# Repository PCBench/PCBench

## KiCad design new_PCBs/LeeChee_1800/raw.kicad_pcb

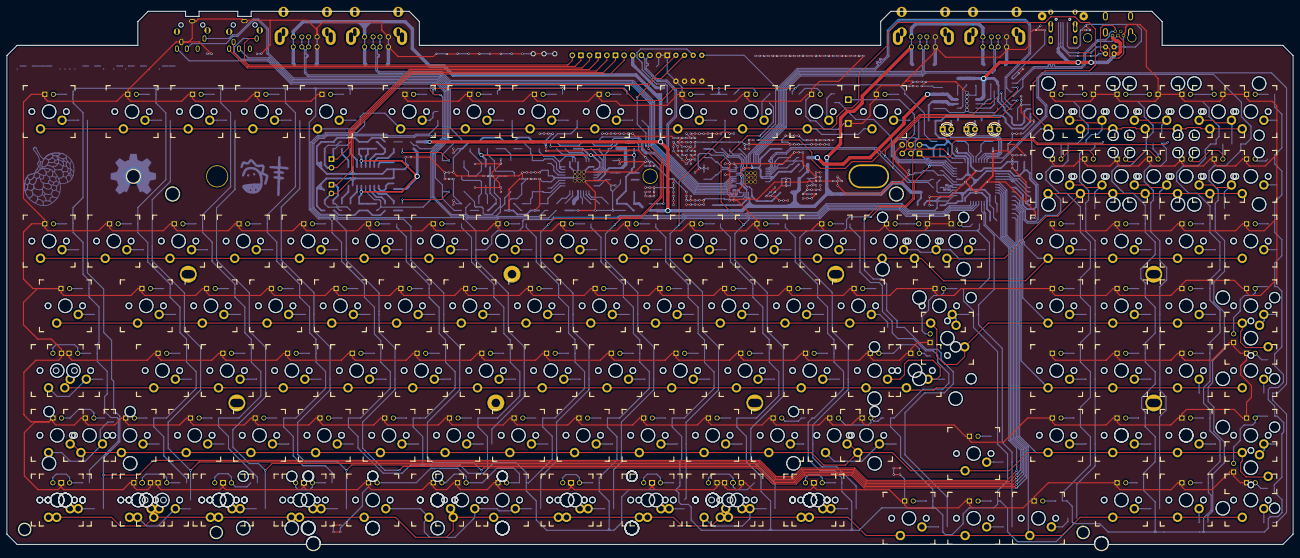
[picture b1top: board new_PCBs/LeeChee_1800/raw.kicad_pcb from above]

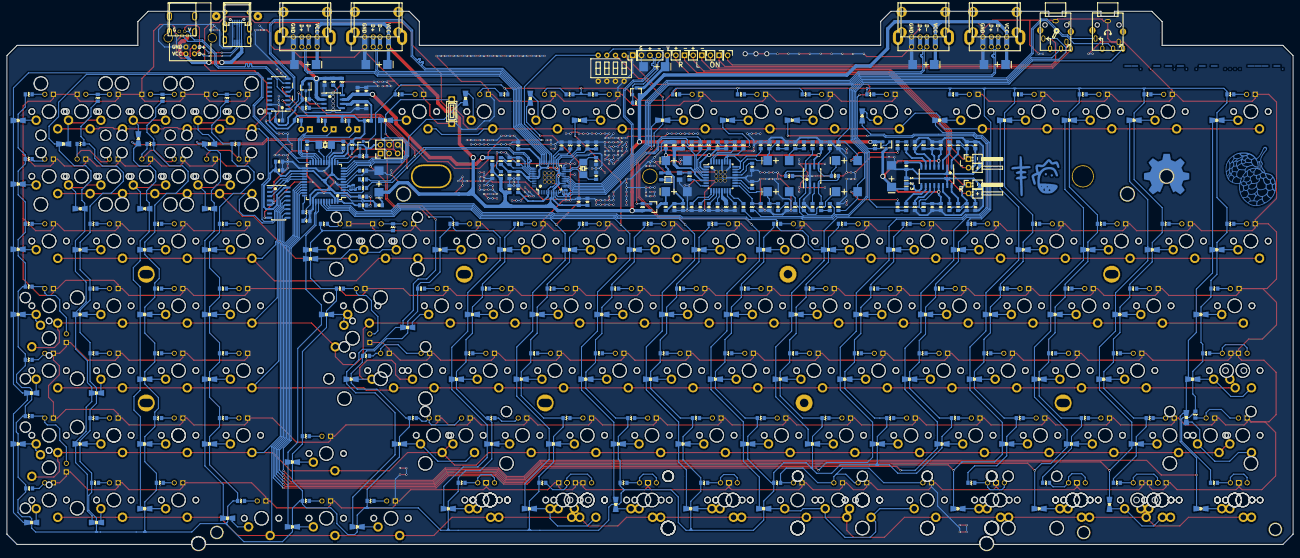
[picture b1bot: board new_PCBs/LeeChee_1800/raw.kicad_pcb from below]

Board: 2 copper layers, 378.4 x 158.6 mm, 557 parts (389 on the bottom side), 358 nets.

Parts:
C1, C2, C73, C74: 22pF; C_0805
C3, C8, C19, C20, C21, C29, C36, C38, C39, C40, C43, C44, C50, C52, C54, C55, C56, C57, C62, C63, C64, C65: 1uF; C_0805
C4, C5, C6, C7, C12, C13, C14, C15, C16, C17, C18, C35, C59, C68, C69, C70, C76: 0.1uF; C_0805
C9, C11, C45, C51, C53: 10uF; C_0805
C10: 4.7uF; C_0805
C22, C23, C24, C25, C26, C27, C28, C41, C42, C58, C75: 100uF; Tantalum_D_7343
C32, C33: 100pF; C_0805
C34, C37: 3.3uF; C_0805
C46, C47, C48, C49: 220pF; C_0805
C60, C61: 22nF; C_0805
C66, C67: 330uF; Tantalum_D_7343
C71, C72: 22uF; C_0805
D1, D2: 1N5817; D_0805
DOWN1: CONN_01X04; Pin_Header_Straight_1x04_Pitch2.54mm
DOWN2, DOWN3, DOWN5, DOWN6: USB_A
DOWN2_2, DOWN3_2, DOWN5_2, DOWN6_2: USB_A; USB_A_10mm
FB1, FB2, FB3, FB4: 2A/120; L_0805
HEADPHONE1: PJ-343
HOLE1: HOLE; OSHW-Symbol_13.4x12mm_Copper
HOLE1_2, HOLE2, HOLE4, HOLE6, HOLE10, HOLE11: HOLE; HOLE_4mm
HOLE3: HOLE; HOLE_6mm
HOLE5: HOLE; HOLE_6X11MM
HOLE7, HOLE8, HOLE9: HOLE; HOLE_3.5mm
J1: JUMP3; JUMP3_0805_Hand
J2: CONN_01X02; Pin_Header_Straight_1x02_Pitch2.54mm
J3: CONN_01X01; Pin_Header_Straight_1x01_Pitch2.54mm
KBD1, KBD2, KBD3, KBD4, KBD5, KBD6, KBD7, KBD8, KBD9, KBD10, KBD11, KBD12, KBD13, KBD14, KBD15, KBD16, KBD17, KBD18, KBD19, KBD20, KBD21, KBD22, KBD23, KBD24, KBD25, KBD26, KBD27, KBD28, KBD29, KBD30, KBD31, KBD32, KBD33, KBD34, KBD35, KBD36, KBD37, KBD38, KBD39, KBD40, KBD41, KBD42, KBD43, KBD44, KBD45, KBD46, KBD47, KBD48, KBD49, KBD50, KBD51, KBD52, KBD53, KBD54, KBD55, KBD56, KBD57, KBD58, KBD59, KBD60, KBD61, KBD62, KBD63, KBD64, KBD65, KBD66, KBD67, KBD68, KBD69, KBD70, KBD71, KBD72, KBD73, KBD74, KBD75, KBD76, KBD77, KBD78, KBD79, KBD80, KBD81, KBD82, KBD83, KBD84, KBD85, KBD86, KBD87, KBD88, KBD89, KBD90, KBD91, KBD92, KBD93, KBD94, KBD95, KBD96, KBD97, KBD98, KBD99, KBD100, KBD101, KBD102, KBD103, KBD104, KBD105, KBD106, KBD107, KBD108: 4148; D_0805&LL4148
KBR1, KBR2, KBR3, KBR4, KBR5, KBR6, KBR7, KBR8, KBR9, KBR10, KBR11, KBR12, KBR13, KBR14, KBR15, KBR16, KBR17, KBR18, KBR19, KBR20, KBR21, KBR22, KBR23, KBR24, KBR25, KBR26, KBR27, KBR28, KBR29, KBR30, KBR31, KBR32, KBR33, KBR34, KBR35, KBR36, KBR37, KBR38, KBR39, KBR40, KBR41, KBR42, KBR43, KBR44, KBR45, KBR46, KBR47, KBR48, KBR49, KBR50, KBR51, KBR52, KBR53, KBR54, KBR55, KBR56, KBR57, KBR58, KBR59, KBR60, KBR61, KBR62, KBR63, KBR64, KBR65, KBR66, KBR67, KBR68, KBR69, KBR70, KBR71, KBR72, KBR73, KBR74, KBR75, KBR76, KBR77, KBR78, KBR79, KBR80, KBR81, KBR82, KBR83, KBR84, KBR85, KBR86, KBR87, KBR88, KBR89, KBR90, KBR91, KBR92, KBR93, KBR94, KBR95, KBR96, KBR97, KBR98, KBR99, KBR100, KBR101, KBR102, KBR103, KBR104, KBR105, KBR106, KBR107, KBR108: 330R; R_0805
KB_ICSP1: AVR-ISP-6; Pin_Header_Straight_2x03_Pitch2.54mm
L1, L2: 1uH; L_0805
LED1, LED2, LED3: LED; LED_D3.0mm
LED5, LED6: LED; LED_0805
MICROPHONE1: PJ-343
MX_0_1, MX_1_1, MX_2_1, MX_3_1, MX_4_1, MX_5_1, MX_6_1, MX_7_1, MX_8_1, MX_9_1, MX_._1: CherryMX; MX1-X-led
MX_'_1: CherryMX; MX1-X-led
MX_,_1: CherryMX; MX1-X-led
MX_-_1: CherryMX; MX1-X-led
MX_/_1: CherryMX; MX1-X-led
MX_;_1: CherryMX; MX1-X-led
MX_=_1: CherryMX; MX1-X-led
MX_ADD_1: CherryMX; MX1-B-led
MX_ADD_2: CherryMX; MX1-X-led
MX_APP_1: CherryMX; MX1-C-led
MX_APP_2: CherryMX; MX1-X-led
MX_APP_3: CherryMX; MX1-B-led
MX_A_1: CherryMX; MX1-X-led
MX_BSPC2: CherryMX; MX1-X-led
MX_BSPC_1: CherryMX; MX1-X-led
MX_BSPC_2: CherryMX; MX1-B-led
MX_B_1: CherryMX; MX1-X-led
MX_CAPS_1: CherryMX; MX1-C-led
MX_CAPS_2: CherryMX; MX1-X-led
MX_C_1: CherryMX; MX1-X-led
MX_DEL_1, MX_DEL_2: CherryMX; MX1-X-led
MX_DOWN_1: CherryMX; MX1-X-led
MX_D_1: CherryMX; MX1-X-led
MX_END_1, MX_END_2: CherryMX; MX1-X-led
MX_ENT_1, MX_ENT_2: CherryMX; MX1-X-led
MX_ESC_1: CherryMX; MX1-X-led
MX_E_1: CherryMX; MX1-X-led
MX_F1_1, MX_F2_1, MX_F3_1, MX_F4_1, MX_F5_1, MX_F6_1, MX_F7_1, MX_F8_1, MX_F9_1, MX_F10_1, MX_F11_1, MX_F12_1: CherryMX; MX1-X-led
MX_FRAME_BSPC_1: MX_FRAME_HOLE; MX_FRAME_2X
MX_FRAME_DEL_1: MX_FRAME_HOLE; MX_FRAME_2X
MX_FRAME_END_1: MX_FRAME_HOLE; MX_FRAME_2X
MX_FRAME_ENT_1: MX_FRAME_HOLE; MX_FRAME_2X
MX_FRAME_HOME_1: MX_FRAME_HOLE; MX_FRAME_2X
MX_FRAME_INS_1: MX_FRAME_HOLE; MX_FRAME_2X
MX_FRAME_LSFT_1: MX_FRAME_HOLE; MX_FRAME_2X
MX_FRAME_P-_1: MX_FRAME_HOLE; MX_FRAME_2X
MX_FRAME_PENT_1: MX_FRAME_HOLE; MX_FRAME_2X
MX_FRAME_PGDN_1: MX_FRAME_HOLE; MX_FRAME_2X
MX_FRAME_PGUP_1: MX_FRAME_HOLE; MX_FRAME_2X
MX_FRAME_RSFT_1: MX_FRAME_HOLE; MX_FRAME_2X
MX_FRAME_SPC_1, MX_FRAME_SPC_2, MX_FRAME_SPC_3: MX_FRAME_HOLE; MX_FRAME_3X
MX_FRAME_SPC_4: MX_FRAME_HOLE; MX_FRAME_6X
MX_FRAME_SPC_5: MX_FRAME_HOLE; MX_FRAME_6.25X
MX_FRAME_SPC_6: MX_FRAME_HOLE; MX_FRAME_7X
MX_FRAME_\_1: MX_FRAME_HOLE; MX_FRAME_2X
MX_F_1: CherryMX; MX1-X-led
MX_GRV_1: CherryMX; MX1-X-led
MX_G_1: CherryMX; MX1-X-led
MX_HOME_1: CherryMX; MX1-X-led
MX_HOME_2: CherryMX; MX1-B-led
MX_H_1: CherryMX; MX1-X-led
MX_INS_1: CherryMX; MX1-X-led
MX_INS_2: CherryMX; MX1-B-led
MX_I_1: CherryMX; MX1-X-led
MX_J_1: CherryMX; MX1-X-led
MX_K_1: CherryMX; MX1-X-led
MX_LALT_1: CherryMX; MX1-B-led
MX_LALT_2: CherryMX; MX1-X-led
MX_LCTL_1: CherryMX; MX1-B-led
MX_LCTL_2: CherryMX; MX1-X-led
MX_LEFT_1: CherryMX; MX1-X-led
MX_LGUI_1: CherryMX; MX1-A-led
MX_LGUI_2: CherryMX; MX1-C-led
MX_LGUI_3: CherryMX; MX1-X-led
MX_LSFT2: CherryMX; MX1-X-led
MX_LSFT_1: CherryMX; MX1-A-led
MX_LSFT_2: CherryMX; MX1-X-led
MX_L_1: CherryMX; MX1-X-led
MX_M_1: CherryMX; MX1-X-led
MX_NLCK_1: CherryMX; MX1-X-led
MX_N_1: CherryMX; MX1-X-led
MX_O_1: CherryMX; MX1-X-led
MX_P0_1, MX_P1_1, MX_P2_1, MX_P3_1, MX_P4_1, MX_P5_1, MX_P6_1, MX_P7_1, MX_P8_1, MX_P9_1, MX_P._1: CherryMX; MX1-X-led
MX_P*_1: CherryMX; MX1-X-led
MX_P+_1: CherryMX; MX1-X-led
MX_P-_1, MX_P-_2: CherryMX; MX1-X-led
MX_P/_1: CherryMX; MX1-X-led
MX_PAUS_1: CherryMX; MX1-X-led
MX_PENT2: CherryMX; MX1-X-led
MX_PENT_1, MX_PENT_2: CherryMX; MX1-X-led
MX_PGDN_1, MX_PGDN_2: CherryMX; MX1-X-led
MX_PGUP_1: CherryMX; MX1-X-led
MX_PGUP_2: CherryMX; MX1-B-led
MX_PRSC_1: CherryMX; MX1-X-led
MX_P_1: CherryMX; MX1-X-led
MX_Q_1: CherryMX; MX1-X-led
MX_RALT_1: CherryMX; MX1-B-led
MX_RALT_2: CherryMX; MX1-X-led
MX_RCTL_1: CherryMX; MX1-B-led
MX_RCTL_2: CherryMX; MX1-X-led
MX_RGHT_1: CherryMX; MX1-X-led
MX_RGUI_1: CherryMX; MX1-B-led
MX_RGUI_2: CherryMX; MX1-X-led
MX_RSFT_1: CherryMX; MX1-A-led
MX_RSFT_2: CherryMX; MX1-X-led
MX_R_1: CherryMX; MX1-X-led
MX_SLCK_1: CherryMX; MX1-X-led
MX_SPC_1, MX_SPC_3, MX_SPC_4: CherryMX; MX1-X-led
MX_SPC_2: CherryMX; MX1-A-led
MX_S_1: CherryMX; MX1-X-led
MX_TAB_1: CherryMX; MX1-X-led
MX_T_1: CherryMX; MX1-X-led
MX_UP_1: CherryMX; MX1-X-led
MX_U_1: CherryMX; MX1-X-led
MX_V_1: CherryMX; MX1-X-led
MX_W_1: CherryMX; MX1-X-led
MX_X_1: CherryMX; MX1-X-led
MX_Y_1: CherryMX; MX1-X-led
MX_Z_1: CherryMX; MX1-X-led
MX_[_1: CherryMX; MX1-X-led
MX_\_1, MX_\_2: CherryMX; MX1-X-led
MX_]_1: CherryMX; MX1-X-led
Q1, Q2, Q3, Q4, Q5: SI2305; SOT-23
R1, R2: 22R; R_0805
R3, R4, R5, R26, R27, R28, R42, R43, R44, R45, R46, R47: 10kR; R_0805
R6, R7, R8: 330R; R_0805
R9, R12: 100kR; R_0805
R10: 2.7kR; R_0805
R11: 47kR; R_0805
R13, R14: 33R; R_0805
R15: 1.5kR; R_0805
R17: 1kR; R_0805
R18, R19, R20, R21: 3.3kR; R_0805
R22, R23: 820R; R_0805
R24, R39, R40: 0R; R_0805
R25, R48: 10R; R_0805
R29, R30: 16R; R_0805
R31, R32, R33, R34, R35, R36: 20kR; R_0805
R37, R38: 100R; R_0805
R41: 10KR; R_0805
SP1, SP2: Speaker; Pin_Header_Angled_1x02_Pitch2.54mm
SP1_2, SP2_2: CONN_01X02; Pin_Header_Straight_1x02_Pitch2.54mm
SW2: SWITCH; SWITCH-3X6X2.5_SMD+
SW_ALLIN1: DIP4WAY; SW_DIP_x4_W7.62mm_Slide_LowProfile
U1: CH440G; SOIC-16_3.9x9.9mm_Pitch1.27mm
U2: ATMEGA32U4; TQFP-44_10x10mm_Pitch0.8mm
U3: 74HC138; SOIC-16_3.9x9.9mm_Pitch1.27mm
U4: FE2.1; LQFP-48_7x7mm_Pitch0.5mm
U5: PCM2912A; TQFP-32_7x7mm_Pitch0.8mm
U6: PAM8406; SOIC-16_3.9x9.9mm_Pitch1.27mm
U7: TPA152; SOIC-8_3.9x4.9mm_Pitch1.27mm
U8: TPS2062; SOIC-8_3.9x4.9mm_Pitch1.27mm
USB1: MINI_USB; USB_MINI_4FOOT
USB2: USB_B
USB3: USB_OTG; USB_MICRO_4FOOT_LONG
USB4: USB_OTG; USB_MICRO_4FOOT
Y1: 16MHz; X_SMD_5032-2pin_5.0x3.2mm
Y2: 12MHz; X_SMD_5032-2pin_5.0x3.2mm
Y4: 6MHz; X_SMD_5032-4pin_5.0x3.2mm

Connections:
/3TO8IO1: U2.25, U3.1
/3TO8IO2: U2.26, U3.2
/3TO8IO3: U2.27, U3.3
/COL1: KBD1.2, KBD23.2, KBD41.2, KBD60.2, KBD77.2, KBD95.2, U2.36
/COL2: KBD2.2, KBD24.2, KBD42.2, KBD61.2, KBD78.2, KBD96.2, U2.32
/COL3: KBD3.2, KBD25.2, KBD43.2, KBD62.2, KBD79.2, KBD97.2, U2.31
/COL4: KBD4.2, KBD26.2, KBD45.2, KBD63.2, KBD80.2, KBD98.2, U2.30
/COL5: KBD5.2, KBD27.2, KBD46.2, KBD64.2, KBD81.2, U2.29
/COL6: KBD6.2, KBD28.2, KBD47.2, KBD65.2, KBD82.2, U2.28
/COL7: KBD7.2, KBD29.2, KBD48.2, KBD66.2, KBD83.2, U2.1
/COL8: KBD8.2, KBD30.2, KBD49.2, KBD67.2, KBD84.2, KBD99.2, U2.41
/COL9: KBD9.2, KBD31.2, KBD50.2, KBD68.2, KBD85.2, KBD100.2, U2.40
/COL10: KBD10.2, KBD32.2, KBD51.2, KBD69.2, KBD86.2, KBD101.2, U2.39
/COL11: KBD11.2, KBD33.2, KBD52.2, KBD70.2, KBD87.2, KBD102.2, U2.38
/COL12: KBD12.2, KBD34.2, KBD53.2, KBD71.2, KBD88.2, KBD103.2, U2.8
/COL13: KBD13.2, KBD35.2, KBD54.2, KBD72.2, KBD89.2, KBD104.2, KB_ICSP1.3, U2.9
/COL14: KBD18.2, KBD36.2, KBD55.2, KBD90.2, KBD105.2, U2.37
/COL15: KBD14.2, KBD19.2, KBD37.2, KBD56.2, KBD73.2, KBD91.2, KBD106.2, KB_ICSP1.4, U2.10
/COL16: KBD15.2, KBD20.2, KBD38.2, KBD57.2, KBD74.2, KBD92.2, KBD107.2, KB_ICSP1.1, U2.11
/COL17: KBD16.2, KBD21.2, KBD39.2, KBD58.2, KBD75.2, KBD93.2, KBD108.2, U2.22
/COL18: KBD17.2, KBD22.2, KBD40.2, KBD44.2, KBD59.2, KBD76.2, KBD94.2, U2.21
/DC5V: C10.1, C13.1, C23.1, C24.1, C26.1, C27.1, C28.1, D2.2, DOWN2.1, DOWN2_2.1, DOWN3.1, DOWN3_2.1, DOWN5.1, DOWN5_2.1, DOWN6.1, DOWN6_2.1, L1.1, Q2.2, Q4.2, Q5.2, R11.2, R41.1, R42.2, R47.2, U4.8
/DOWN1+: DOWN1.3, U4.19
/DOWN1-: DOWN1.2, U4.18
/DOWN1_DC5V: C22.1, DOWN1.1, Q2.3
/DOWN2+: DOWN2.3, DOWN2_2.3, U4.17
/DOWN2-: DOWN2.2, DOWN2_2.2, U4.16
/DOWN3+: DOWN3.3, DOWN3_2.3, U4.14
/DOWN3-: DOWN3.2, DOWN3_2.2, U4.13
/DOWN4+: R14.1, R15.1, U4.12
/DOWN4-: R13.1, U4.11
/DOWN5+: DOWN5.3, DOWN5_2.3, U4.33
/DOWN5-: DOWN5.2, DOWN5_2.2, U4.32
/DOWN6+: DOWN6.3, DOWN6_2.3, U4.35
/DOWN6-: DOWN6.2, DOWN6_2.2, U4.34
/DOWN7+: R1.2, U1.3, U4.38
/DOWN7-: R2.2, U1.6, U4.37
/DOWN_1_ON: Q2.1, R42.1, SW_ALLIN1.3
/EN1: Q1.1, R43.2, SW_ALLIN1.4, U1.1, U8.3
/EN2: Q1.3, R44.2, U8.4
/HUBUSBD+: U1.2, U4.30
/HUBUSBD-: U1.5, U4.29
/HUBVCC: C69.2, C71.2, L1.2, U8.7
/HUBX+: C73.1, U4.22, Y2.1
/HUBX-: C74.1, U4.23, Y2.2
/KBBL: Q3.1, R5.2, U2.12
/KBRST: KB_ICSP1.5, R4.2, SW2.1, U2.13
/KBVCC: C4.1, C5.1, C6.1, C7.1, C8.1, D1.1, D2.1, KB_ICSP1.2, Q3.2, R4.1, R5.1, R6.2, R7.2, R8.2, U2.2, U2.7, U2.14, U2.24, U2.34, U2.44, U3.6, U3.16
/KBX+: C1.1, U2.16, Y1.1
/KBX-: C2.1, U2.17, Y1.2
/KD+: R1.1, U2.4
/KD-: R2.1, U2.3
/LED+: KBR1.2, KBR2.2, KBR3.2, KBR4.2, KBR5.2, KBR6.2, KBR7.2, KBR8.2, KBR9.2, KBR10.2, KBR11.2, KBR12.2, KBR13.2, KBR14.2, KBR15.2, KBR16.2, KBR17.2, KBR18.2, KBR19.2, KBR20.2, KBR21.2, KBR22.2, KBR23.2, KBR24.2, KBR25.2, KBR26.2, KBR27.2, KBR28.2, KBR29.2, KBR30.2, KBR31.2, KBR32.2, KBR33.2, KBR34.2, KBR35.2, KBR36.2, KBR37.2, KBR38.2, KBR39.2, KBR40.2, KBR41.2, KBR42.2, KBR43.2, KBR44.2, KBR45.2, KBR46.2, KBR47.2, KBR48.2, KBR49.2, KBR50.2, KBR51.2, KBR52.2, KBR53.2, KBR54.2, KBR55.2, KBR56.2, KBR57.2, KBR58.2, KBR59.2, KBR60.2, KBR61.2, KBR62.2, KBR63.2, KBR64.2, KBR65.2, KBR66.2, KBR67.2, KBR68.2, KBR69.2, KBR70.2, KBR71.2, KBR72.2, KBR73.2, KBR74.2, KBR75.2, KBR76.2, KBR77.2, KBR78.2, KBR79.2, KBR80.2, KBR81.2, KBR82.2, KBR83.2, KBR84.2, KBR85.2, KBR86.2, KBR87.2, KBR88.2, KBR89.2, KBR90.2, KBR91.2, KBR92.2, KBR93.2, KBR94.2, KBR95.2, KBR96.2, KBR97.2, KBR98.2, KBR99.2, KBR100.2, KBR101.2, KBR102.2, KBR103.2, KBR104.2, KBR105.2, KBR106.2, KBR107.2, KBR108.2, Q3.3
/LEDC: LED2.1, U2.19
/LEDN: LED1.1, U2.18
/LEDS: LED3.1, U2.20
/MICMBIAS: MICROPHONE1.R, R17.2
/MICVIN: C37.2, J3.1, MICROPHONE1.L
/PAINL: C55.2, C67.2, HEADPHONE1.L, R38.1
/PAINR: C56.2, C66.2, HEADPHONE1.R, R37.1
/PAMODE: J1.2, U6.9
/PAMUTE: C50.2, C51.2, C52.2, C53.2, C58.1, J1.3, Q4.3, R25.1, R28.1, U6.4, U6.5, U6.13
/PASHDN: HEADPHONE1.ON, R28.2, U6.12
/PA_ON: Q4.1, R47.1, SW_ALLIN1.1
/REXT: R10.1, U4.27
/ROW1: MX_ESC_1.2, MX_F1_1.2, MX_F2_1.2, MX_F3_1.2, MX_F4_1.2, MX_F5_1.2, MX_F6_1.2, MX_F7_1.2, MX_F8_1.2, MX_F9_1.2, MX_F10_1.2, MX_F11_1.2, MX_F12_1.2, MX_HOME_1.2, MX_HOME_2.2, MX_INS_1.2, MX_INS_2.2, MX_PGUP_1.2, MX_PGUP_2.2, MX_PRSC_1.2, U3.15
/ROW2: MX_BSPC2.2, MX_DEL_1.2, MX_DEL_2.2, MX_END_1.2, MX_END_2.2, MX_PGDN_1.2, MX_PGDN_2.2, MX_SLCK_1.2, U3.14
/ROW3: MX_0_1.2, MX_1_1.2, MX_2_1.2, MX_3_1.2, MX_4_1.2, MX_5_1.2, MX_6_1.2, MX_7_1.2, MX_8_1.2, MX_9_1.2, MX_-_1.2, MX_=_1.2, MX_BSPC_1.2, MX_BSPC_2.2, MX_GRV_1.2, MX_NLCK_1.2, MX_P*_1.2, MX_P/_1.2, MX_PAUS_1.2, U3.13
/ROW4: MX_E_1.2, MX_I_1.2, MX_O_1.2, MX_P7_1.2, MX_P8_1.2, MX_P9_1.2, MX_P-_1.2, MX_P-_2.2, MX_P_1.2, MX_Q_1.2, MX_R_1.2, MX_TAB_1.2, MX_T_1.2, MX_U_1.2, MX_W_1.2, MX_Y_1.2, MX_[_1.2, MX_\_1.2, MX_\_2.2, MX_]_1.2, U3.12
/ROW5: MX_'_1.2, MX_;_1.2, MX_A_1.2, MX_CAPS_1.2, MX_CAPS_2.2, MX_D_1.2, MX_ENT_1.2, MX_ENT_2.2, MX_F_1.2, MX_G_1.2, MX_H_1.2, MX_J_1.2, MX_K_1.2, MX_L_1.2, MX_P4_1.2, MX_P5_1.2, MX_P6_1.2, MX_P+_1.2, MX_S_1.2, U3.11
/ROW6: MX_,_1.2, MX_._1.2, MX_/_1.2, MX_B_1.2, MX_C_1.2, MX_LSFT2.2, MX_LSFT_1.2, MX_LSFT_2.2, MX_M_1.2, MX_N_1.2, MX_P1_1.2, MX_P2_1.2, MX_P3_1.2, MX_PENT_1.2, MX_PENT_2.2, MX_RSFT_1.2, MX_RSFT_2.2, MX_UP_1.2, MX_V_1.2, MX_X_1.2, MX_Z_1.2, U3.10
/ROW7: MX_ADD_1.2, MX_ADD_2.2, MX_APP_1.2, MX_APP_2.2, MX_APP_3.2, MX_DOWN_1.2, MX_LALT_1.2, MX_LALT_2.2, MX_LCTL_1.2, MX_LCTL_2.2, MX_LEFT_1.2, MX_LGUI_1.2, MX_LGUI_2.2, MX_LGUI_3.2, MX_P0_1.2, MX_P._1.2, MX_PENT2.2, MX_RALT_1.2, MX_RALT_2.2, MX_RCTL_1.2, MX_RCTL_2.2, MX_RGHT_1.2, MX_RGUI_1.2, MX_RGUI_2.2, MX_SPC_1.2, MX_SPC_2.2, MX_SPC_3.2, MX_SPC_4.2, U3.9
/SCD+: R14.2, U5.4
/SCD-: R13.2, U5.3
/SCDGND: C29.2, R24.1, U5.6
/SCOUTL: C41.2, C63.1, R20.1
/SCOUTR: C42.2, C62.1, R21.2
/SCPLAY: R23.2, U5.32
/SCREC: R22.2, U5.31
/SCVCC: C25.1, L2.2, Q5.3
/SCVCC2: C44.2, C45.1, C65.2, C75.1, C76.1, L2.1, LED5.2, LED6.2, U5.2, U7.6, Y4.4
/SCX+: R48.1, U5.8
/SC_ON: Q5.1, R41.2, SW_ALLIN1.2
/USBD+: U1.4, USB1.3, USB2.3, USB3.3, USB4.3
/USBD-: U1.7, USB1.2, USB2.2, USB3.2, USB4.2
/USBVCC: C59.1, C68.2, Q1.2, R43.1, R45.1, R46.2, U1.16, U8.2, USB1.1, USB2.1, USB3.1, USB4.1
/V18: C11.1, C19.1, C20.1, C21.1, U4.6, U4.21, U4.25, U4.28
/V33: C9.1, C14.1, C15.1, C16.1, C17.1, C18.1, R9.2, U4.9, U4.15, U4.20, U4.26, U4.31, U4.36, U4.42, U4.43, U4.45
/VBUSM: R11.1, R12.1, U4.41
/XRSTJ: C12.1, R9.1, U4.40
Earth: C1.2, C2.2, C3.2, C4.2, C5.2, C6.2, C7.2, C8.2, C9.2, C10.2, C11.2, C12.2, C13.2, C14.2, C15.2, C16.2, C17.2, C18.2, C19.2, C20.2, C21.2, C22.2, C23.2, C24.2, C25.2, C26.2, C27.2, C28.2, C32.2, C33.2, C34.2, C35.2, C36.2, C38.2, C39.1, C40.2, C43.2, C44.1, C45.2, C46.2, C47.1, C48.1, C49.2, C50.1, C51.1, C52.1, C53.1, C54.2, C57.2, C58.2, C59.2, C64.2, C65.1, C68.1, C69.1, C70.2, C71.1, C72.2, C73.2, C74.2, C75.2, C76.2, DOWN1.4, DOWN2.4, DOWN2_2.4, DOWN3.4, DOWN3_2.4, DOWN5.4, DOWN5_2.4, DOWN6.4, DOWN6_2.4, HEADPHONE1.G, HEADPHONE1.OS, J1.1, KB_ICSP1.6, MICROPHONE1.G, MX_0_1.4, MX_1_1.4, MX_2_1.4, MX_3_1.4, MX_4_1.4, MX_5_1.4, MX_6_1.4, MX_7_1.4, MX_8_1.4, MX_9_1.4, MX_'_1.4, MX_,_1.4, MX_-_1.4, MX_._1.4, MX_/_1.4, MX_;_1.4, MX_=_1.4, MX_ADD_1.4, MX_ADD_2.4, MX_APP_1.4, MX_APP_2.4, MX_APP_3.4, MX_A_1.4, MX_BSPC2.4, MX_BSPC_1.4, MX_BSPC_2.4, MX_B_1.4, MX_CAPS_1.4, MX_CAPS_2.4, MX_C_1.4, MX_DEL_1.4, MX_DEL_2.4, MX_DOWN_1.4, MX_D_1.4, MX_END_1.4, MX_END_2.4, MX_ENT_1.4, MX_ENT_2.4, MX_ESC_1.4, MX_E_1.4, MX_F1_1.4, MX_F2_1.4, MX_F3_1.4, MX_F4_1.4, MX_F5_1.4, MX_F6_1.4, MX_F7_1.4, MX_F8_1.4, MX_F9_1.4, MX_F10_1.4, MX_F11_1.4, MX_F12_1.4, MX_F_1.4, MX_GRV_1.4, MX_G_1.4, MX_HOME_1.4, MX_HOME_2.4, MX_H_1.4, MX_INS_1.4, MX_INS_2.4, MX_I_1.4, MX_J_1.4, MX_K_1.4, MX_LALT_1.4, MX_LALT_2.4, MX_LCTL_1.4, MX_LCTL_2.4, MX_LEFT_1.4, MX_LGUI_1.4, MX_LGUI_2.4, MX_LGUI_3.4, MX_LSFT2.4, MX_LSFT_1.4, MX_LSFT_2.4, MX_L_1.4, MX_M_1.4, MX_NLCK_1.4, MX_N_1.4, MX_O_1.4, MX_P0_1.4, MX_P1_1.4, MX_P2_1.4, MX_P3_1.4, MX_P4_1.4, MX_P5_1.4, MX_P6_1.4, MX_P7_1.4, MX_P8_1.4, MX_P9_1.4, MX_P*_1.4, MX_P+_1.4, MX_P-_1.4, MX_P-_2.4, MX_P._1.4, MX_P/_1.4, MX_PAUS_1.4, MX_PENT2.4, MX_PENT_1.4, MX_PENT_2.4, MX_PGDN_1.4, MX_PGDN_2.4, MX_PGUP_1.4, MX_PGUP_2.4, MX_PRSC_1.4, MX_P_1.4, MX_Q_1.4, MX_RALT_1.4, MX_RALT_2.4, MX_RCTL_1.4, MX_RCTL_2.4, MX_RGHT_1.4, MX_RGUI_1.4, MX_RGUI_2.4, MX_RSFT_1.4, MX_RSFT_2.4, MX_R_1.4, MX_SLCK_1.4, MX_SPC_1.4, MX_SPC_2.4, MX_SPC_3.4, MX_SPC_4.4, MX_S_1.4, MX_TAB_1.4, MX_T_1.4, MX_UP_1.4, MX_U_1.4, MX_V_1.4, MX_W_1.4, MX_X_1.4, MX_Y_1.4, MX_Z_1.4, MX_[_1.4, MX_\_1.4, MX_\_2.4, MX_]_1.4, R3.1, R10.2, R12.2, R18.2, R19.1, R20.2, R21.1, R24.2, R29.1, R30.2, R33.2, R34.2, R37.2, R38.2, R39.2, R40.2, R44.1, SW2.2, SW_ALLIN1.5, SW_ALLIN1.6, SW_ALLIN1.7, SW_ALLIN1.8, U1.8, U1.15, U2.5, U2.15, U2.23, U2.35, U2.43, U3.4, U3.5, U3.8, U4.10, U4.24, U4.39, U5.1, U5.20, U5.25, U5.28, U6.2, U6.15, U7.2, U7.7, U8.1, USB1.5, USB2.4, USB3.5, USB4.5, Y4.2
unnamed: C3.1, U2.6
unnamed: C29.1, R15.2, U5.5
unnamed: C32.1, U5.9
unnamed: C33.1, U5.10
unnamed: C34.1, U5.11
unnamed: C35.1, U5.12
unnamed: C36.1, U5.15
unnamed: C37.1, U5.16
unnamed: C38.1, R17.1, U5.17
unnamed: C39.2, U5.19
unnamed: C40.1, U5.21
unnamed: C41.1, C61.1, R18.1, U5.18
unnamed: C42.1, C60.2, R19.2, U5.22
unnamed: C43.1, U5.23, U5.24, U5.26, U5.27
unnamed: C46.1, FB2.1, SP1.2, SP1_2.2
unnamed: C47.2, FB1.1, SP1.1, SP1_2.1
unnamed: C48.2, FB3.1, SP2.2, SP2_2.2
unnamed: C49.1, FB4.1, SP2.1, SP2_2.1
unnamed: C54.1, R25.2, U6.6
unnamed: C55.1, R26.1
unnamed: C56.1, R27.1
unnamed: C57.1, U6.8
unnamed: C60.1, R29.2
unnamed: C61.2, R30.1
unnamed: C62.2, R31.2
unnamed: C63.2, R32.2
unnamed: C64.1, U7.3
unnamed: C66.1, R33.1, R35.2, U7.1
unnamed: C67.1, R34.1, R36.1, U7.5
unnamed: C70.1, C72.1, D1.2, U8.6
unnamed: FB1.2, U6.3
unnamed: FB2.2, U6.1
unnamed: FB3.2, U6.16
unnamed: FB4.2, U6.14
unnamed: J2.1, MICROPHONE1.OS
unnamed: J2.2, MICROPHONE1.ON
unnamed: KBD1.1, MX_ESC_1.1
unnamed: KBD2.1, MX_F1_1.1
unnamed: KBD3.1, MX_F2_1.1
unnamed: KBD4.1, MX_F3_1.1
unnamed: KBD5.1, MX_F4_1.1
unnamed: KBD6.1, MX_F5_1.1
unnamed: KBD7.1, MX_F6_1.1
unnamed: KBD8.1, MX_F7_1.1
unnamed: KBD9.1, MX_F8_1.1
unnamed: KBD10.1, MX_F9_1.1
unnamed: KBD11.1, MX_F10_1.1
unnamed: KBD12.1, MX_F11_1.1
unnamed: KBD13.1, MX_F12_1.1
unnamed: KBD14.1, MX_INS_1.1, MX_INS_2.1
unnamed: KBD15.1, MX_HOME_1.1, MX_HOME_2.1
unnamed: KBD16.1, MX_PGUP_1.1, MX_PGUP_2.1
unnamed: KBD17.1, MX_PRSC_1.1
unnamed: KBD18.1, MX_BSPC2.1
unnamed: KBD19.1, MX_DEL_1.1, MX_DEL_2.1
unnamed: KBD20.1, MX_END_1.1, MX_END_2.1
unnamed: KBD21.1, MX_PGDN_1.1, MX_PGDN_2.1
unnamed: KBD22.1, MX_SLCK_1.1
unnamed: KBD23.1, MX_GRV_1.1
unnamed: KBD24.1, MX_1_1.1
unnamed: KBD25.1, MX_2_1.1
unnamed: KBD26.1, MX_3_1.1
unnamed: KBD27.1, MX_4_1.1
unnamed: KBD28.1, MX_5_1.1
unnamed: KBD29.1, MX_6_1.1
unnamed: KBD30.1, MX_7_1.1
unnamed: KBD31.1, MX_8_1.1
unnamed: KBD32.1, MX_9_1.1
unnamed: KBD33.1, MX_0_1.1
unnamed: KBD34.1, MX_-_1.1
unnamed: KBD35.1, MX_=_1.1
unnamed: KBD36.1, MX_BSPC_1.1, MX_BSPC_2.1
unnamed: KBD37.1, MX_NLCK_1.1
unnamed: KBD38.1, MX_P/_1.1
unnamed: KBD39.1, MX_P*_1.1
unnamed: KBD40.1, MX_PAUS_1.1
unnamed: KBD41.1, MX_TAB_1.1
unnamed: KBD42.1, MX_Q_1.1
unnamed: KBD43.1, MX_W_1.1
unnamed: KBD44.1, MX_PENT2.1
unnamed: KBD45.1, MX_E_1.1
unnamed: KBD46.1, MX_R_1.1
unnamed: KBD47.1, MX_T_1.1
unnamed: KBD48.1, MX_Y_1.1
unnamed: KBD49.1, MX_U_1.1
unnamed: KBD50.1, MX_I_1.1
unnamed: KBD51.1, MX_O_1.1
unnamed: KBD52.1, MX_P_1.1
unnamed: KBD53.1, MX_[_1.1
unnamed: KBD54.1, MX_]_1.1
unnamed: KBD55.1, MX_\_1.1, MX_\_2.1
unnamed: KBD56.1, MX_P7_1.1
unnamed: KBD57.1, MX_P8_1.1
unnamed: KBD58.1, MX_P9_1.1
unnamed: KBD59.1, MX_P-_1.1, MX_P-_2.1
unnamed: KBD60.1, MX_CAPS_1.1, MX_CAPS_2.1
unnamed: KBD61.1, MX_A_1.1
unnamed: KBD62.1, MX_S_1.1
unnamed: KBD63.1, MX_D_1.1
unnamed: KBD64.1, MX_F_1.1
unnamed: KBD65.1, MX_G_1.1
unnamed: KBD66.1, MX_H_1.1
unnamed: KBD67.1, MX_J_1.1
unnamed: KBD68.1, MX_K_1.1
unnamed: KBD69.1, MX_L_1.1
unnamed: KBD70.1, MX_;_1.1
unnamed: KBD71.1, MX_'_1.1
unnamed: KBD72.1, MX_ENT_1.1, MX_ENT_2.1
unnamed: KBD73.1, MX_P4_1.1
unnamed: KBD74.1, MX_P5_1.1
unnamed: KBD75.1, MX_P6_1.1
unnamed: KBD76.1, MX_P+_1.1
unnamed: KBD77.1, MX_LSFT_1.1, MX_LSFT_2.1
unnamed: KBD78.1, MX_LSFT2.1
unnamed: KBD79.1, MX_Z_1.1
unnamed: KBD80.1, MX_X_1.1
unnamed: KBD81.1, MX_C_1.1
unnamed: KBD82.1, MX_V_1.1
unnamed: KBD83.1, MX_B_1.1
unnamed: KBD84.1, MX_N_1.1
unnamed: KBD85.1, MX_M_1.1
unnamed: KBD86.1, MX_,_1.1
unnamed: KBD87.1, MX_._1.1
unnamed: KBD88.1, MX_/_1.1
unnamed: KBD89.1, MX_RSFT_1.1, MX_RSFT_2.1
unnamed: KBD90.1, MX_UP_1.1
unnamed: KBD91.1, MX_P1_1.1
unnamed: KBD92.1, MX_P2_1.1
unnamed: KBD93.1, MX_P3_1.1
unnamed: KBD94.1, MX_PENT_1.1, MX_PENT_2.1
unnamed: KBD95.1, MX_LCTL_1.1, MX_LCTL_2.1
unnamed: KBD96.1, MX_LGUI_1.1, MX_LGUI_2.1, MX_LGUI_3.1
unnamed: KBD97.1, MX_LALT_1.1, MX_LALT_2.1
unnamed: KBD98.1, MX_ADD_1.1, MX_ADD_2.1
unnamed: KBD99.1, MX_SPC_1.1, MX_SPC_2.1, MX_SPC_3.1, MX_SPC_4.1
unnamed: KBD100.1, MX_RALT_1.1, MX_RALT_2.1
unnamed: KBD101.1, MX_RGUI_1.1, MX_RGUI_2.1
unnamed: KBD102.1, MX_APP_1.1, MX_APP_2.1, MX_APP_3.1
unnamed: KBD103.1, MX_RCTL_1.1, MX_RCTL_2.1
unnamed: KBD104.1, MX_LEFT_1.1
unnamed: KBD105.1, MX_DOWN_1.1
unnamed: KBD106.1, MX_RGHT_1.1
unnamed: KBD107.1, MX_P0_1.1
unnamed: KBD108.1, MX_P._1.1
unnamed: KBR1.1, MX_ESC_1.3
unnamed: KBR2.1, MX_F1_1.3
unnamed: KBR3.1, MX_F2_1.3
unnamed: KBR4.1, MX_F3_1.3
unnamed: KBR5.1, MX_F4_1.3
unnamed: KBR6.1, MX_F5_1.3
unnamed: KBR7.1, MX_F6_1.3
unnamed: KBR8.1, MX_F7_1.3
unnamed: KBR9.1, MX_F8_1.3
unnamed: KBR10.1, MX_F9_1.3
unnamed: KBR11.1, MX_F10_1.3
unnamed: KBR12.1, MX_F11_1.3
unnamed: KBR13.1, MX_F12_1.3
unnamed: KBR14.1, MX_INS_1.3, MX_INS_2.3
unnamed: KBR15.1, MX_HOME_1.3, MX_HOME_2.3
unnamed: KBR16.1, MX_PGUP_1.3, MX_PGUP_2.3
unnamed: KBR17.1, MX_PRSC_1.3
unnamed: KBR18.1, MX_BSPC2.3
unnamed: KBR19.1, MX_DEL_1.3, MX_DEL_2.3
unnamed: KBR20.1, MX_END_1.3, MX_END_2.3
unnamed: KBR21.1, MX_PGDN_1.3, MX_PGDN_2.3
unnamed: KBR22.1, MX_SLCK_1.3
unnamed: KBR23.1, MX_GRV_1.3
unnamed: KBR24.1, MX_1_1.3
unnamed: KBR25.1, MX_2_1.3
unnamed: KBR26.1, MX_3_1.3
unnamed: KBR27.1, MX_4_1.3
unnamed: KBR28.1, MX_5_1.3
unnamed: KBR29.1, MX_6_1.3
unnamed: KBR30.1, MX_7_1.3
unnamed: KBR31.1, MX_8_1.3
unnamed: KBR32.1, MX_9_1.3
unnamed: KBR33.1, MX_0_1.3
unnamed: KBR34.1, MX_-_1.3
unnamed: KBR35.1, MX_=_1.3
unnamed: KBR36.1, MX_BSPC_1.3, MX_BSPC_2.3
unnamed: KBR37.1, MX_NLCK_1.3
unnamed: KBR38.1, MX_P/_1.3
unnamed: KBR39.1, MX_P*_1.3
unnamed: KBR40.1, MX_PAUS_1.3
unnamed: KBR41.1, MX_TAB_1.3
unnamed: KBR42.1, MX_Q_1.3
unnamed: KBR43.1, MX_W_1.3
unnamed: KBR44.1, MX_PENT2.3
unnamed: KBR45.1, MX_E_1.3
unnamed: KBR46.1, MX_R_1.3
unnamed: KBR47.1, MX_T_1.3
unnamed: KBR48.1, MX_Y_1.3
unnamed: KBR49.1, MX_U_1.3
unnamed: KBR50.1, MX_I_1.3
unnamed: KBR51.1, MX_O_1.3
unnamed: KBR52.1, MX_P_1.3
unnamed: KBR53.1, MX_[_1.3
unnamed: KBR54.1, MX_]_1.3
unnamed: KBR55.1, MX_\_1.3, MX_\_2.3
unnamed: KBR56.1, MX_P7_1.3
unnamed: KBR57.1, MX_P8_1.3
unnamed: KBR58.1, MX_P9_1.3
unnamed: KBR59.1, MX_P-_1.3, MX_P-_2.3
unnamed: KBR60.1, MX_CAPS_1.3, MX_CAPS_2.3
unnamed: KBR61.1, MX_A_1.3
unnamed: KBR62.1, MX_S_1.3
unnamed: KBR63.1, MX_D_1.3
unnamed: KBR64.1, MX_F_1.3
unnamed: KBR65.1, MX_G_1.3
unnamed: KBR66.1, MX_H_1.3
unnamed: KBR67.1, MX_J_1.3
unnamed: KBR68.1, MX_K_1.3
unnamed: KBR69.1, MX_L_1.3
unnamed: KBR70.1, MX_;_1.3
unnamed: KBR71.1, MX_'_1.3
unnamed: KBR72.1, MX_ENT_1.3, MX_ENT_2.3
unnamed: KBR73.1, MX_P4_1.3
unnamed: KBR74.1, MX_P5_1.3
unnamed: KBR75.1, MX_P6_1.3
unnamed: KBR76.1, MX_P+_1.3
unnamed: KBR77.1, MX_LSFT_1.3, MX_LSFT_2.3
unnamed: KBR78.1, MX_LSFT2.3
unnamed: KBR79.1, MX_Z_1.3
unnamed: KBR80.1, MX_X_1.3
unnamed: KBR81.1, MX_C_1.3
unnamed: KBR82.1, MX_V_1.3
unnamed: KBR83.1, MX_B_1.3
unnamed: KBR84.1, MX_N_1.3
unnamed: KBR85.1, MX_M_1.3
unnamed: KBR86.1, MX_,_1.3
unnamed: KBR87.1, MX_._1.3
unnamed: KBR88.1, MX_/_1.3
unnamed: KBR89.1, MX_RSFT_1.3, MX_RSFT_2.3
unnamed: KBR90.1, MX_UP_1.3
unnamed: KBR91.1, MX_P1_1.3
unnamed: KBR92.1, MX_P2_1.3
unnamed: KBR93.1, MX_P3_1.3
unnamed: KBR94.1, MX_PENT_1.3, MX_PENT_2.3
unnamed: KBR95.1, MX_LCTL_1.3, MX_LCTL_2.3
unnamed: KBR96.1, MX_LGUI_1.3, MX_LGUI_2.3, MX_LGUI_3.3
unnamed: KBR97.1, MX_LALT_1.3, MX_LALT_2.3
unnamed: KBR98.1, MX_ADD_1.3, MX_ADD_2.3
unnamed: KBR99.1, MX_SPC_1.3, MX_SPC_2.3, MX_SPC_3.3, MX_SPC_4.3
unnamed: KBR100.1, MX_RALT_1.3, MX_RALT_2.3
unnamed: KBR101.1, MX_RGUI_1.3, MX_RGUI_2.3
unnamed: KBR102.1, MX_APP_1.3, MX_APP_2.3, MX_APP_3.3
unnamed: KBR103.1, MX_RCTL_1.3, MX_RCTL_2.3
unnamed: KBR104.1, MX_LEFT_1.3
unnamed: KBR105.1, MX_DOWN_1.3
unnamed: KBR106.1, MX_RGHT_1.3
unnamed: KBR107.1, MX_P0_1.3
unnamed: KBR108.1, MX_P._1.3
unnamed: LED1.2, R6.1
unnamed: LED2.2, R7.1
unnamed: LED3.2, R8.1
unnamed: LED5.1, R23.1
unnamed: LED6.1, R22.1
unnamed: R3.2, U2.33
unnamed: R26.2, U6.7
unnamed: R27.2, U6.10
unnamed: R31.1, R35.1, U7.8
unnamed: R32.1, R36.2, U7.4
unnamed: R39.1, U5.13
unnamed: R40.1, U6.11
unnamed: R45.2, U8.8
unnamed: R46.1, U8.5
unnamed: R48.2, Y4.3

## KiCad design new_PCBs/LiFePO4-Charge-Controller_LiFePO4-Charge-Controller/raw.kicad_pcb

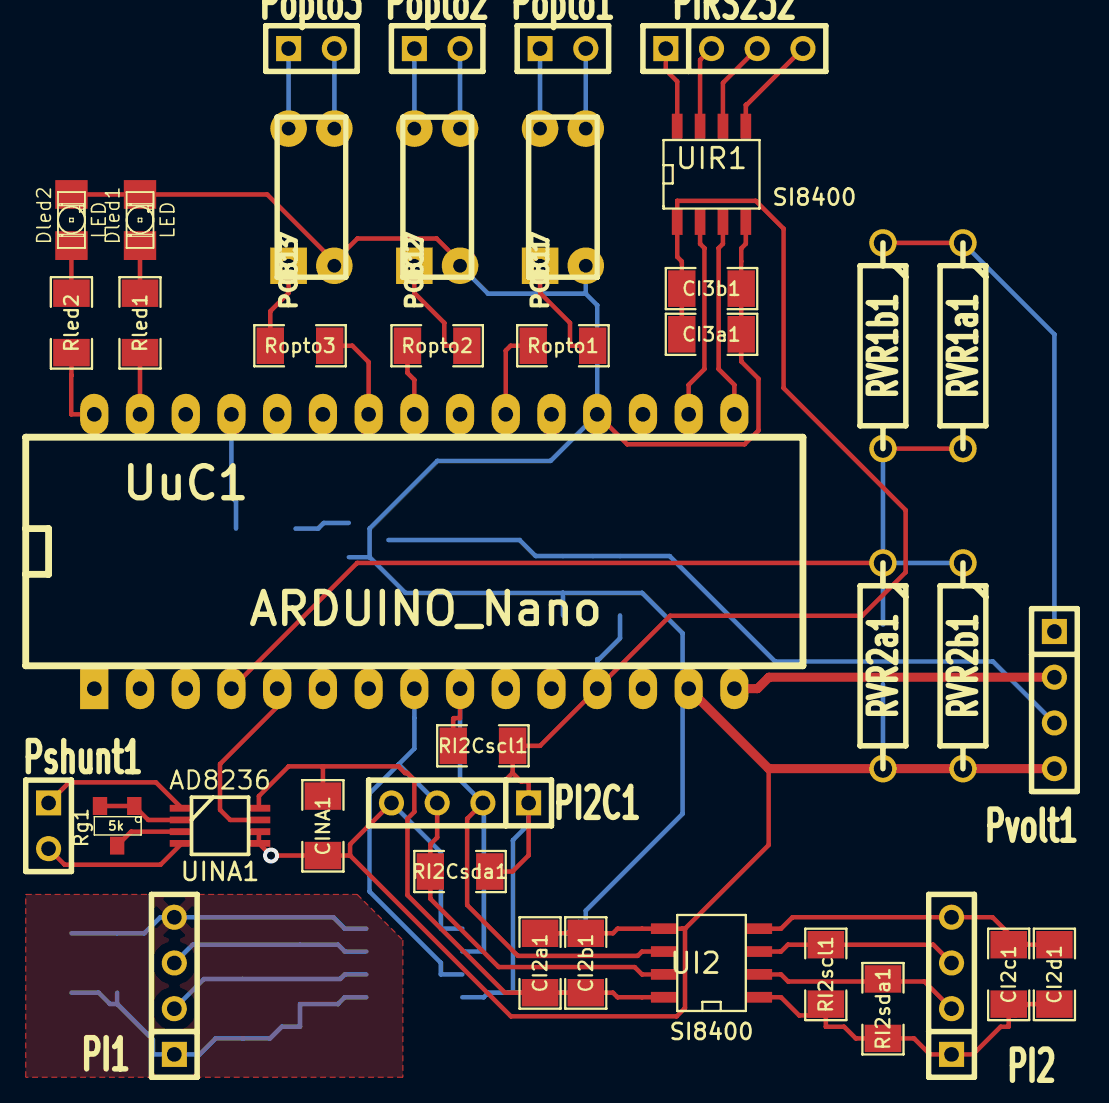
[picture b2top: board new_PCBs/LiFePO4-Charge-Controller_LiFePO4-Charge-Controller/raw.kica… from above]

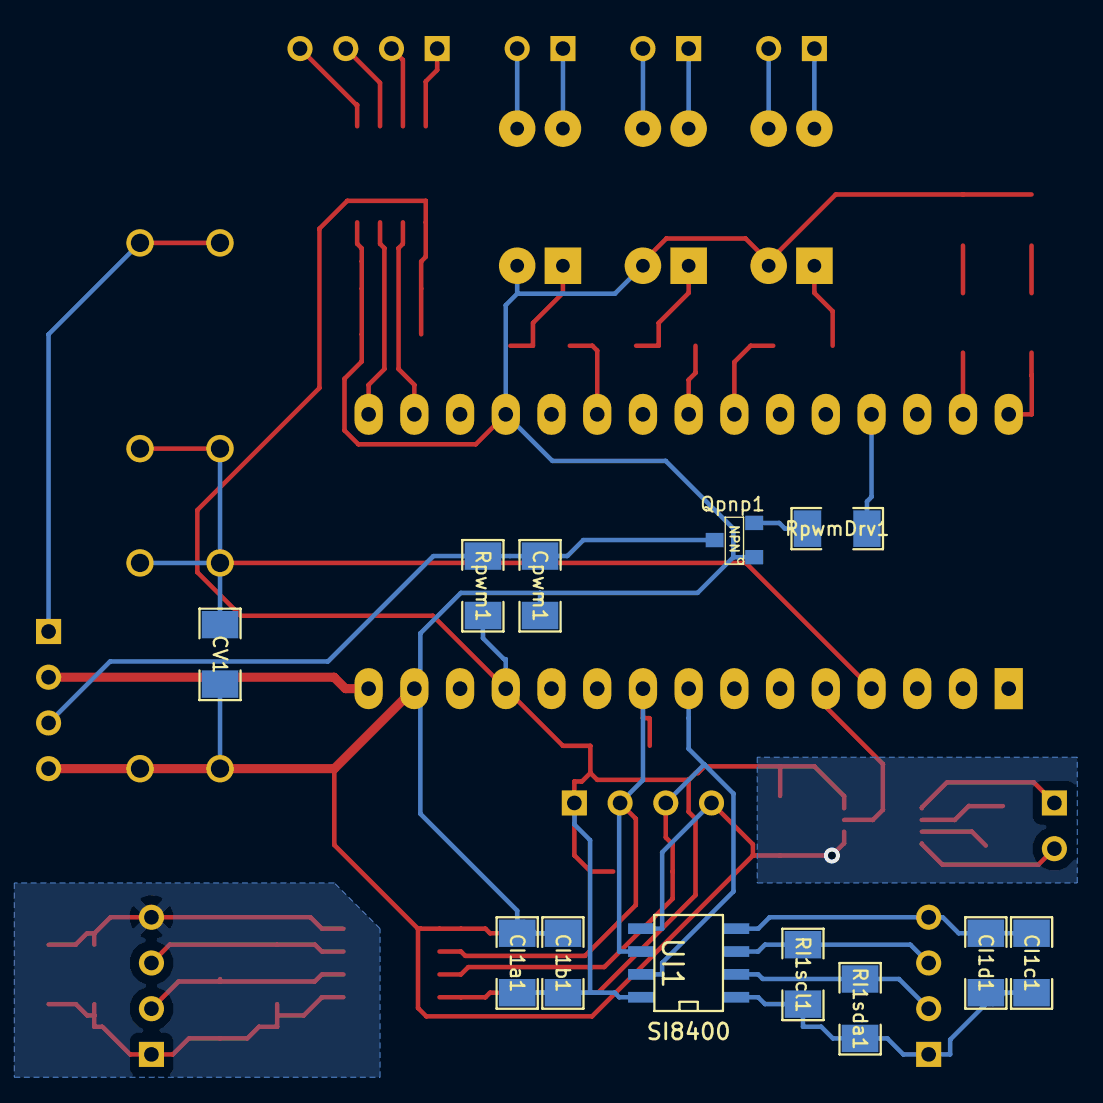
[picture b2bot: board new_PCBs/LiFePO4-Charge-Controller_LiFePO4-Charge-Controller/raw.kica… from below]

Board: 2 copper layers, 51 parts (12 on the bottom side), 45 nets.

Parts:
CI1a1, CI1c1, CI2a1, CI2c1, CI3a1: 100nF; SM1206
CI1b1, CI1d1, CI2b1, CI2d1, CI3b1: 1uF; SM1206
CINA1: 100nF; SM1206
CV1: 10pF; SM1206
Cpwm1: 300nF; SM1206
Dled1, Dled2: LED; LED-1206
OC1, OC2, OC3: PC817; DIP-4
PI1, PI2, PI2C1: I2C; SIL-4
PIRS232: RS232; SIL-4
Popto1, Popto2, Popto3: opto; SIL-2
Pshunt1: differential; SIL-2
Pvolt1: Gnd PWM 12V B+; SIL-4
Qpnp1: NPN; SOT23
RI1scl1, RI1sda1, RI2scl1, RI2sda1: 5k; SM1206
RI2Cscl1, RI2Csda1: 1.8k; SM1206
RVR1a1, RVR1b1: 99k; R4-5
RVR2a1, RVR2b1: 1k; R4-5
Rg1: 5k; SOT23
Rled1: 1k; SM1206
Rled2: 1K; SM1206
Ropto1, Ropto2, Ropto3: 1k; SM1206
Rpwm1: 120; SM1206
RpwmDrv1: 560; SM1206
UI1, UI2: SI8400; SO8E
UINA1: AD8236; MSOP_8
UIR1: SI8400; SO8E
UuC1: ARDUINO_Nano; arduino_mini

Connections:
5v: CI1a1.1, CI1b1.1, CI2a1.1, CI2b1.1, CI3a1.2, CI3b1.2, CINA1.1, PI2C1.1, RI2Cscl1.1, RI2Csda1.1, Rpwm1.2, UI1.8, UI2.8, UINA1.8, UIR1.1, UuC1.12
D3: Ropto1.1, UuC1.21
D5: Ropto2.1, UuC1.23
D6: Ropto3.1, UuC1.24
Gnd: CI1a1.2, CI1b1.2, CI2a1.2, CI2b1.2, CI3a1.1, CI3b1.1, CINA1.2, CV1.2, Cpwm1.2, Dled1.2, Dled2.2, OC1.2, OC2.2, OC3.2, PI2C1.4, Pvolt1.4, Qpnp1.1, RVR2a1.2, RVR2b1.2, UI1.5, UI2.5, UINA1.5, UINA1.6, UIR1.4, UuC1.14, UuC1.19
I2C1_GND: CI1c1.2, CI1d1.2, PI1.4, UI1.4
I2C2_GND: CI2c1.2, CI2d1.2, PI2.4, UI2.4
unnamed: UIR1.2, UuC1.17
unnamed: UIR1.3, UuC1.16
unnamed: PI1.3, RI1scl1.2, UI1.3
unnamed: PI1.2, RI1sda1.2, UI1.2
unnamed: PI2.2, RI2sda1.2, UI2.2
unnamed: CV1.1, RVR1a1.2, RVR1b1.2, RVR2a1.1, RVR2b1.1, UuC1.4
unnamed: PIRS232.3, UIR1.6
unnamed: PIRS232.2, UIR1.7
unnamed: PIRS232.1, UIR1.8
unnamed: PI2.3, RI2scl1.2, UI2.3
unnamed: OC1.4, Popto1.1
unnamed: OC3.4, Popto3.1
unnamed: OC3.1, Ropto3.2
unnamed: OC2.3, Popto2.2
unnamed: OC2.4, Popto2.1
unnamed: OC2.1, Ropto2.2
unnamed: OC1.3, Popto1.2
unnamed: OC3.3, Popto3.2
unnamed: OC1.1, Ropto1.2
unnamed: Cpwm1.1, Pvolt1.3, Qpnp1.3, Rpwm1.1
unnamed: Qpnp1.2, RpwmDrv1.2
unnamed: Dled1.1, Rled1.2
unnamed: Dled2.1, Rled2.2
unnamed: RpwmDrv1.1, UuC1.27
unnamed: Rled2.1, UuC1.30
unnamed: Rled1.1, UuC1.29
unnamed: Rg1.1, Rg1.2, UINA1.2
unnamed: UINA1.7, UuC1.5
unnamed: Pshunt1.2, UINA1.4
unnamed: Pshunt1.1, UINA1.1
unnamed: Rg1.3, UINA1.3
unnamed: Pvolt1.2, UuC1.15
unnamed: CI2c1.1, CI2d1.1, PI2.1, RI2scl1.1, RI2sda1.1, UI2.1
unnamed: CI1c1.1, CI1d1.1, PI1.1, RI1scl1.1, RI1sda1.1, UI1.1
unnamed: PI2C1.3, RI2Csda1.2, UI1.7, UI2.7, UuC1.8
unnamed: PI2C1.2, RI2Cscl1.2, UI1.6, UI2.6, UuC1.9
unnamed: Pvolt1.1, RVR1a1.1, RVR1b1.1
RS232_GND: PIRS232.4, UIR1.5

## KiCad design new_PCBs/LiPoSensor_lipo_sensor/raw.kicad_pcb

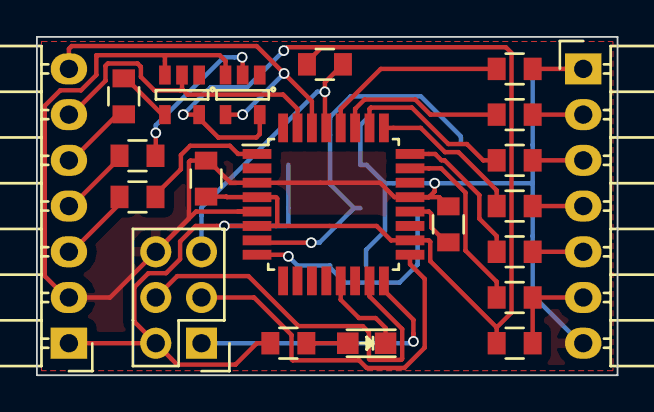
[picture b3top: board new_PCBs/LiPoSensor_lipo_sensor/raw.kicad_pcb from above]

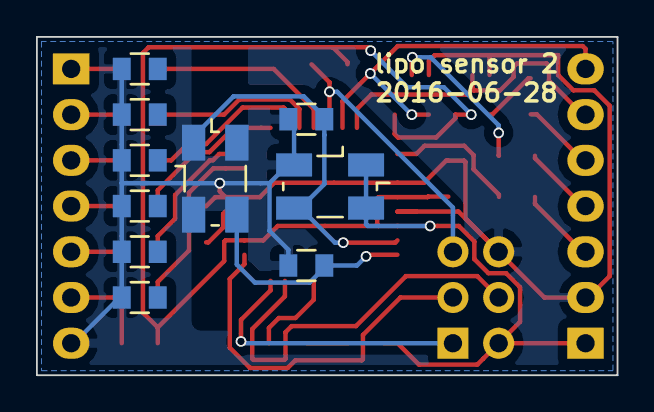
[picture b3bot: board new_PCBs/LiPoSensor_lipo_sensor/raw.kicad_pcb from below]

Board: 2 copper layers, 32.3 x 18.8 mm, 31 parts (10 on the bottom side), 31 nets.

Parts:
5k1: 4k7; C_0805
C1, C3: 100nF; C_0805
C2, C5: 22pF; C_0805
D1: LED; LED_0805
IC1: ATMEGA328P-A; TQFP-32_7x7mm_Pitch0.8mm
P1: CONN_02X03; Pin_Header_Straight_2x03
P2, P3: CONN_01X07; Pin_Header_Angled_1x07
P4: OSZILLATOR; Oszillator_SMD_5032_4Pads
P5, P6: INVERTER; SOT-23-5
P7: QUARZ; Oszillator_SMD_5032_4Pads
R1: 680; C_0805
R2, R5, R9: 22k; C_0805
R3, R6: 1k; C_0805
R4: 0; C_0805
R7: 18k; C_0805
R8: 1k2; C_0805
R10: 1k8; C_0805
R11: 15k; C_0805
R12: 2k2; C_0805
R13: 12k; C_0805
R14: 3k9; C_0805
R15, R17: R; C_0805
R16: 10k; C_0805

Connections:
/Cell1: IC1.23, R13.2, R14.1
/Cell2: IC1.24, R11.2, R12.1
/Cell3: IC1.25, R9.2, R10.1
/Cell4: IC1.26, R7.2, R8.1
/Cell5: IC1.27, R5.2, R6.1
/Cell6: IC1.28, R2.2, R3.1
/LED: D1.1, IC1.13
/RX: IC1.30, P2.7, P6.4
/S.Port: 5k1.2, IC1.1
/TX: IC1.31, P2.6, P5.2
GND: C1.2, C2.1, C3.1, C5.1, IC1.3, IC1.5, IC1.21, P1.6, P2.2, P3.7, P4.2, P5.3, P6.3, R3.2, R6.2, R8.2, R10.2, R12.2, R14.2
unnamed: 5k1.1, P2.3
unnamed: C2.2, IC1.7, P4.3, P7.1
unnamed: C3.2, IC1.20
unnamed: C5.2, IC1.8, P7.3
unnamed: D1.2, R1.2
unnamed: IC1.15, P1.4
unnamed: IC1.16, P1.1
unnamed: IC1.17, P1.3
unnamed: IC1.29, P1.5, R16.2
unnamed: P2.4, R17.2
unnamed: P2.5, R15.2
unnamed: P3.1, R2.1
unnamed: P3.2, R5.1
unnamed: P3.3, R7.1
unnamed: P3.4, R9.1
unnamed: P3.5, R11.1
unnamed: P3.6, R4.2, R13.1
unnamed: P5.4, R15.1
unnamed: P6.2, R17.1
VCC: C1.1, IC1.4, IC1.6, IC1.18, P1.2, P2.1, P4.1, P4.4, P5.5, P6.5, R1.1, R4.1, R16.1

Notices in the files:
new_PCBs/Librecalc-Hardware_calc/raw.kicad_pcb:
Copyright Pierre Parent & Ael Gain
This is open hardware, you can use it under Cern Open Hardware License 1.2
